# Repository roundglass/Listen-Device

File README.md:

# Roundglass Sustain Listen : Realtime Acoustic

## Monitoring

- **_Listen_** ​ is a modular acoustic station (device) and software / program to analyze sounds
- **_Listen_** ​is an end-end solution to collect sounds on the ground to infer intelligence
- **_Listen_** differs from other acoustic stations available in the market in its ease-of-use,
    set-up and portability
- It relies on solar-power, long-lasting battery and a plug-n-play communication system
    that would transmit data real-time to a console or App or Web interface.
- The data will be available real-time on smartphone/tablet through an application and
    would enable users to make informed decisions. Potential users are conservation and
    law enforcement personnel (forest department primarily) and NGOs and local
    communities who are interested in conserving their natural heritage.
- The app has capabilities to view data as graphs and in other forms of visualization. (Ex:
    used to observe trend of data over a requested time period like the sound
    characteristics.

## How does ​ Listen ​ work?

### Listen: working illustration

Listen isolates ‘sounds-of-interest’ from the surrounding or ambient sound. Sounds-of-interest
can be defined according to our needs - gunshots, dynamite blasts, motor vehicles, timber
felling, etc. The unit(Listen Mote) is installed in field and designed to blend in with the
surroundings - hidden in the tree canopy, etc. This can stay deployed for at least 4 weeks
without a battery change. There exists an option to connect it to a solar charger for longer
deployments. 

High-sensitivity microphones coupled with a data transmission system form the
field unit (Listen Mote). Information is received at a base station over cellular network.
The audio recording based on the programmed recording frequency is uploaded to our cloud
database which is linked to our cloud based virtual analytics system, once the system
determines that a particular recording is of interest (anomaly in the environment) then an alert is
sent out to the respective authority.

We foresee a need for these devices in the coming years owing to increased awareness
regarding conservation issues and also due to severe shortage of enforcement and patrol
personnel guarding our protected areas.

## Hardware 

### Roundglass Sustain Listen: components

**Microphones** ​: A high sensitivity microphone is used that will work for far field listening and has
digital gain to isolate noise amplification as in analog signal amplification.

**Form factor:** ​ Easy to conceal, hard shell polycarbonate, rounded edges, matte finish, no
external wiring or protruding antenna.

**Power source:** ​Solar powered with alternate power input for seasons and places with no
adequate solar radiation.

**Battery** ​: Li-ion pack can stay powered and deployed in field for at least 4 weeks without charge.

**Communication** ​: Wireless (GSM)

**Data** ​: App and Web based monitoring, configurable frequency and format of logging and
transmission.

**Switches** ​: Waterproof, dust-proof and insect-proof. No external switches.

**Mounting** ​: Compact system can be mounted on a mast or tripod of your choice.

## Technical Specifications

**Communication** ​: Global GSM

**Temperature** ​: -20 to 60 C

**Weatherproof** ​: IP 66/

**Battery:** ​ Rechargeable Li-ion battery.

**Solar Panel:** ​ Optional

**Alternate Power source** ​: Can plug a 6-12V external DC power supply (Optional)

**Application:** ​Android and iOS

## Applications

Protected areas are often vast, remote, with difficult terrain and severely understaffed to
effectively monitor and protect. With Roundglass Sustain Listen, we hope to plug in some of these gaps to
effectively monitor large areas and identify threats.

1. Detection of gunshots in protected areas - poaching and hunting increasingly rely on
    guns and is one of the leading causes of wildlife decline
2. Detection of dynamite fishing along rivers - illegal and highly destructive. The
    conservation and livelihood impacts of dynamite fishing is enormous
3. Detection of vehicular movement in protected areas - motor vehicles are used to illegally
    access areas for poaching, hunting and timber smuggling.
4. Another potential application (which we hope to address at a later date) is detection of
    wildfires

## Highlights​:

1. Detects, locates and alerts on threat sounds in less than 60 seconds.

2. Simple, affordable subscription service — no IT integration required

3. Get notified on your existing mobile phone via SMS / App notification.

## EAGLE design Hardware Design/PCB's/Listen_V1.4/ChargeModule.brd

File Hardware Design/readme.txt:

#Hardware Design

Schematics and PCB Design

Platform Eagle

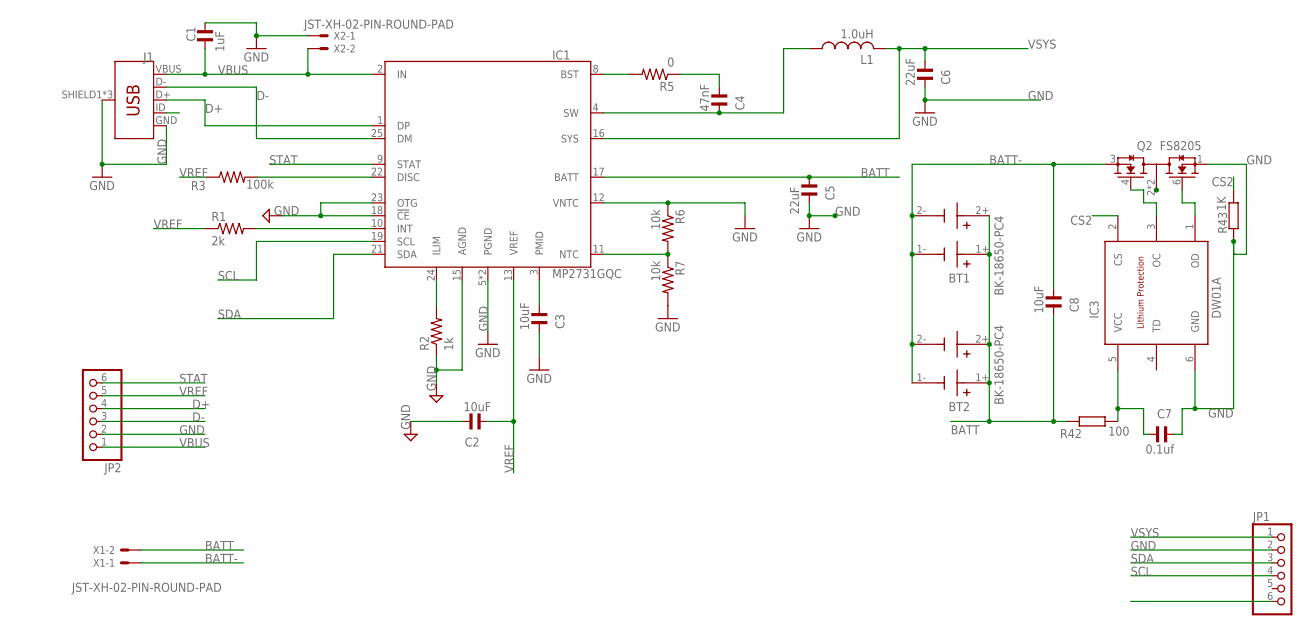
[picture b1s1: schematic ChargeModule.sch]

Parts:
BT1, BT2: BK-18650-PC4; BAT_BK-18650-PC4
C1: 1uF; RC-MASTER-SMD_C0805MP
C2, C3, C8: 10uF; RC-MASTER-SMD_C0805MP
C4: 47nF; RC-MASTER-SMD_C0805MP
C5, C6: 22uF; RC-MASTER-SMD_C0805MP
C7: 0.1uf; RC-MASTER-SMD_C0805MP
IC1: MP2731GQC; QFN-26-3.5
IC3: DW01A; SOT23-6
J1: USB_MICRO-B_FEMALE-SMT; USB-B-MICRO-SMD
JP1, JP2: PINHD-1X6JSTXH; JST-XH-06-PACKAGE-ROUND-PAD
L1: 1.0uH; POWER-CHOKE_WE-TPC
Q2: FS8205; SOT95P280X145-6N
R1: 2k; M0805
R2: 1k; M0805
R3: 100k; M0805
R5: 0; M0805
R6, R7: 10k; M0805
R42: 100; R0805
R43: 1K; R0805
X1, X2: JST-XH-02-PIN-ROUND-PAD; JST-XH-02-PACKAGE-ROUND-PAD

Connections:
BATT: BT1.1+, BT1.2+, BT2.1+, BT2.2+, C5.1, C8.2, IC1.17 (BATT), R42.2, X1.2
BATT-: BT1.1-, BT1.2-, BT2.1-, BT2.2-, C8.1, Q2.3 (S2), X1.1
CS2: IC3.2 (CS), R43.1
D+: IC1.1 (DP), J1.D+, JP2.4
D-: IC1.25 (DM), J1.D-, JP2.3
GND: C1.2, C2.2, C3.2, C5.2, C6.2, C7.2, IC1.5 (PGND), IC1.6 (PGND), IC1.12 (VNTC), IC1.15 (AGND), IC1.18 (!CE), IC1.23 (OTG), IC3.6 (GND), J1.GND, J1.SHIELD1 (SHIELD), J1.SHIELD2 (SHIELD), J1.SHIELD3 (SHIELD), JP1.2, JP2.2, Q2.1 (S1), R2.1, R6.1, R7.2, R43.2, X2.1
unnamed: IC1.24 (ILIM), R2.2
unnamed: IC1.10 (INT), R1.2
unnamed: IC1.22 (DISC), R3.2
unnamed: IC1.8 (BST), R5.2
unnamed: C3.1, IC1.3 (PMID)
unnamed: C4.1, R5.1
unnamed: C4.2, IC1.4 (SW), L1.1
unnamed: IC1.11 (NTC), R6.2, R7.1
unnamed: Q2.2 (D12), Q2.5 (D12)
unnamed: C7.1, IC3.5 (VCC), R42.1
unnamed: IC3.1 (OD), Q2.6 (G1)
unnamed: IC3.3 (OC), Q2.4 (G2)
SCL: IC1.19 (SCL), JP1.4
SDA: IC1.21 (SDA), JP1.3
STAT: IC1.9 (STAT), JP2.6
VBUS: C1.1, IC1.2 (IN), J1.VBUS, JP2.1, X2.2
VREF: C2.1, IC1.13 (VREF), JP2.5, R1.1, R3.1
VSYS: C6.1, IC1.16 (SYS), JP1.1, L1.2

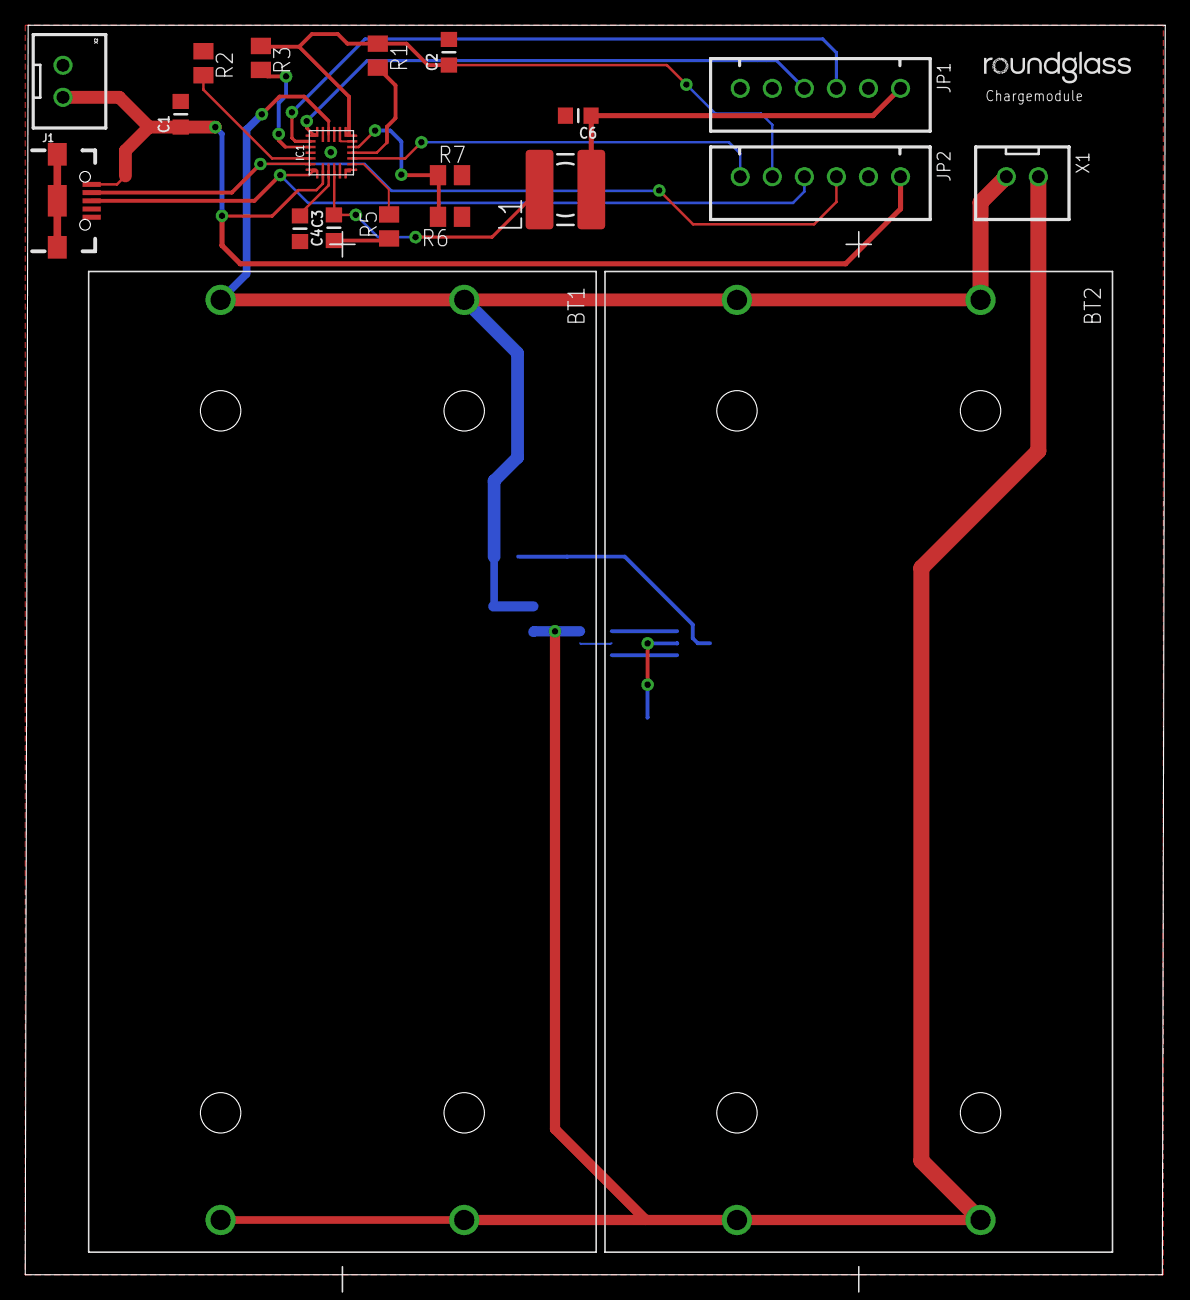
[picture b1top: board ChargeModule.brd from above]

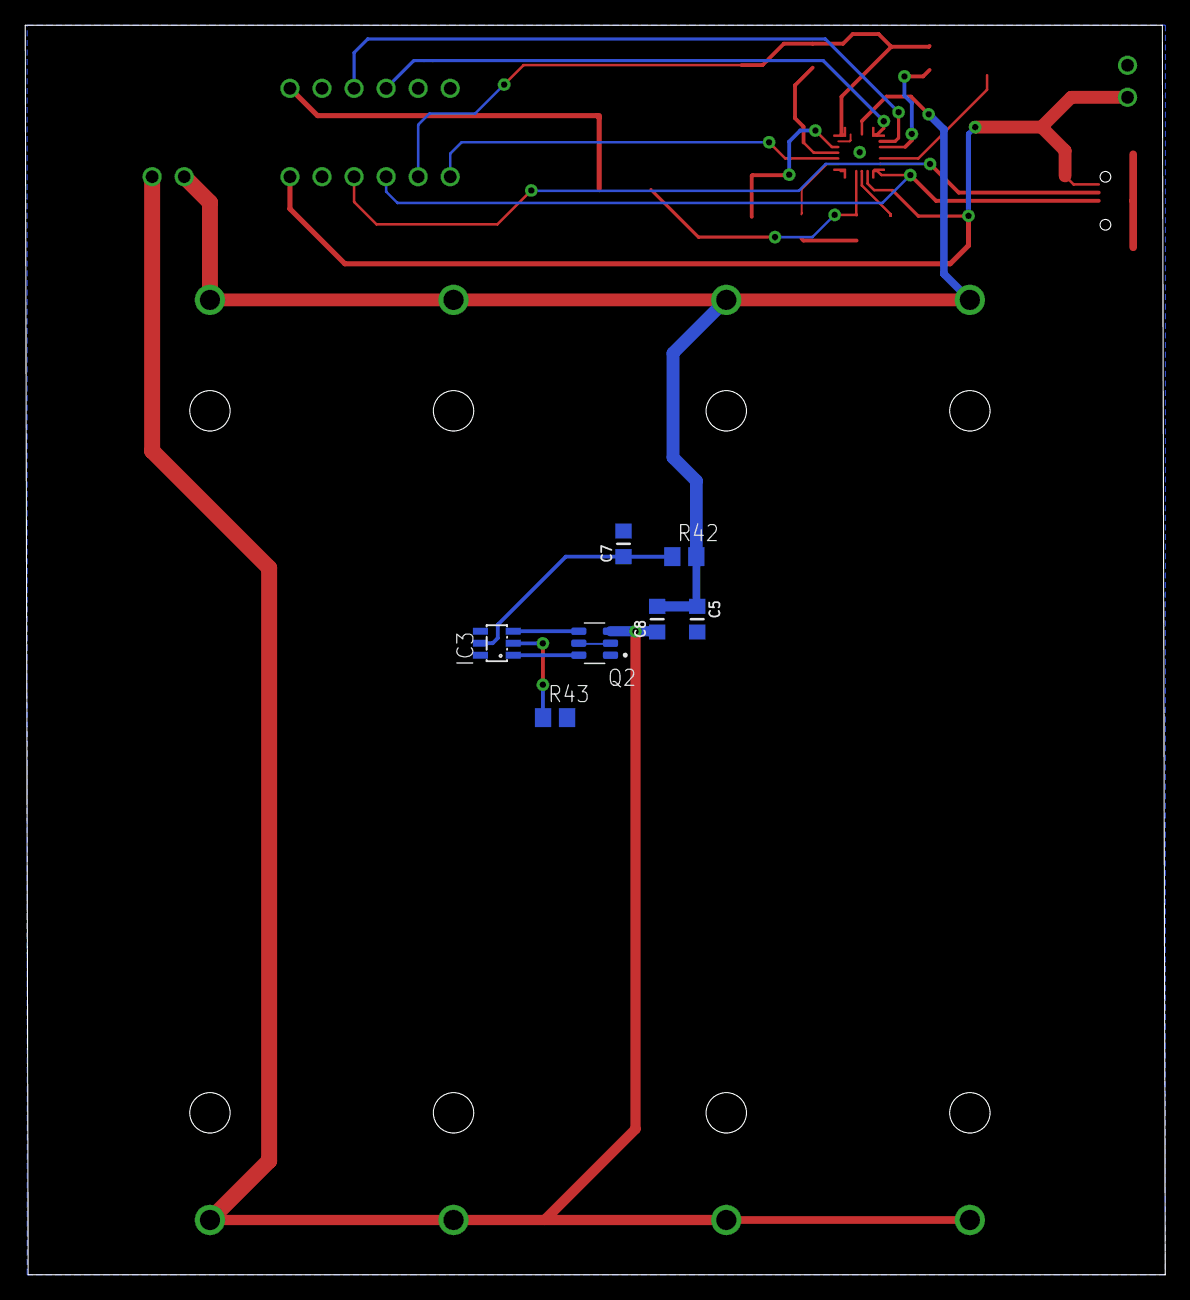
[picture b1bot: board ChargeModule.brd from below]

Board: 2 copper layers, 90.3 x 99.0 mm, 27 parts (7 on the bottom side), 24 nets.

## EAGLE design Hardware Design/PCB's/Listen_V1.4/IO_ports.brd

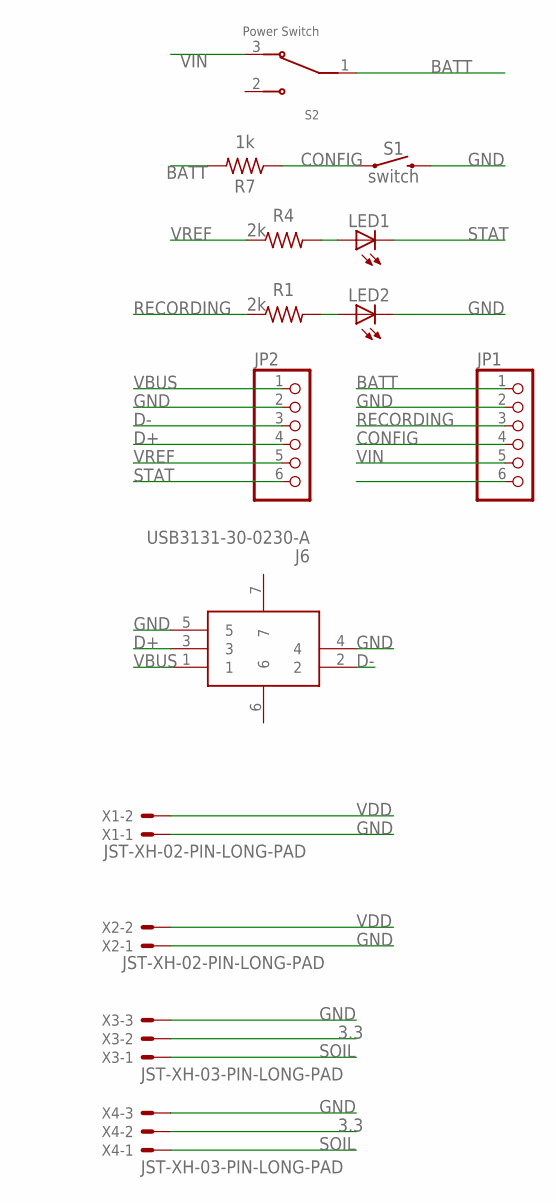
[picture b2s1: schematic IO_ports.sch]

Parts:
J6: USB3131-30-0230-A; USB3131300230A
JP1, JP2: PINHD-1X6JSTXH; JST-XH-06-PACKAGE-ROUND-PAD
LED1, LED2: LEDCHIP-LED0805; CHIP-LED0805
R1, R4: 2k; M0805
R7: 1k; RESC2012X65
S1: switch; TACTILE_SWITCH_PTH_6.0MM
S2: Power Switch; SW_MSS-102545-28A-D
X1, X2: JST-XH-02-PIN-LONG-PAD; JST-XH-02-PACKAGE-LONG-PAD
X3, X4: JST-XH-03-PIN-LONG-PAD; JST-XH-03-PACKAGE-LONG-PAD

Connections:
3.3: X3.2, X4.2
BATT: JP1.1, R7.2, S2.1
CONFIG: JP1.4, R7.1, S1.1
D+: J6.3, JP2.4
D-: J6.2, JP2.3
GND: J6.4, J6.5, JP1.2, JP2.2, LED2.C, S1.3 (2), X1.1, X2.1, X3.3, X4.3
unnamed: LED2.A, R1.2
unnamed: LED1.A, R4.2
RECORDING: JP1.3, R1.1
SOIL: X3.1, X4.1
STAT: JP2.6, LED1.C
VBUS: J6.1, JP2.1
VDD: X1.2, X2.2
VIN: JP1.5, S2.3
VREF: JP2.5, R4.1

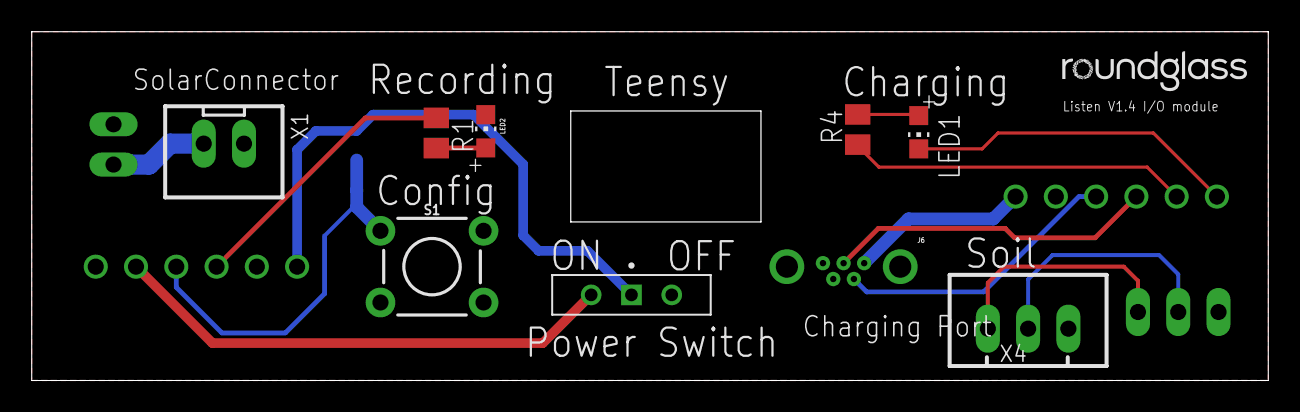
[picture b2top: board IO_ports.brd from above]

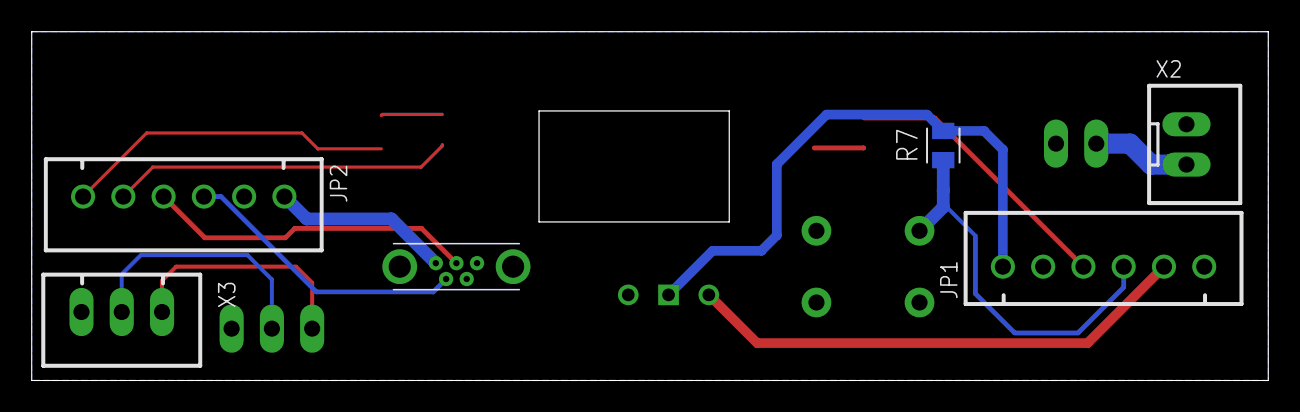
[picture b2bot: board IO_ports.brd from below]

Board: 2 copper layers, 78.0 x 22.0 mm, 14 parts (6 on the bottom side), 15 nets.

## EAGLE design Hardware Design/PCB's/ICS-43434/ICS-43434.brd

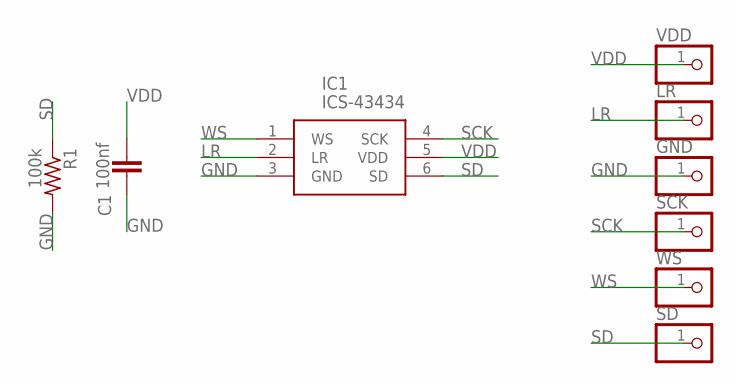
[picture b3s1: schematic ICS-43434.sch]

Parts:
C1: 100nf; CAP_0805
GND: PINHD-1X1CB; 1X01-CLEANBIG
IC1: ICS-43434; ICS43434
LR: PINHD-1X1CB; 1X01-CLEANBIG
R1: 100k; R0805
SCK: PINHD-1X1CB; 1X01-CLEANBIG
SD: PINHD-1X1CB; 1X01-CLEANBIG
VDD: PINHD-1X1CB; 1X01-CLEANBIG
WS: PINHD-1X1CB; 1X01-CLEANBIG

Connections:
GND: C1.1, GND.1, IC1.3 (GND), R1.2
LR: IC1.2 (LR), LR.1
SCK: IC1.4 (SCK), SCK.1
SD: IC1.6 (SD), R1.1, SD.1
VDD: C1.2, IC1.5 (VDD), VDD.1
WS: IC1.1 (WS), WS.1

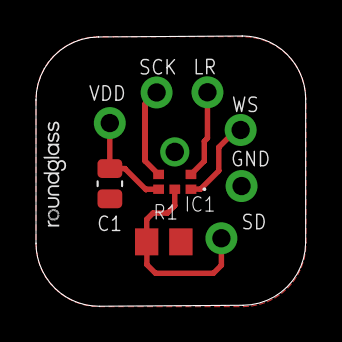
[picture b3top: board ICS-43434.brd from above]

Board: 2 copper layers, 15.0 x 15.0 mm, 9 parts (0 on the bottom side), 6 nets.

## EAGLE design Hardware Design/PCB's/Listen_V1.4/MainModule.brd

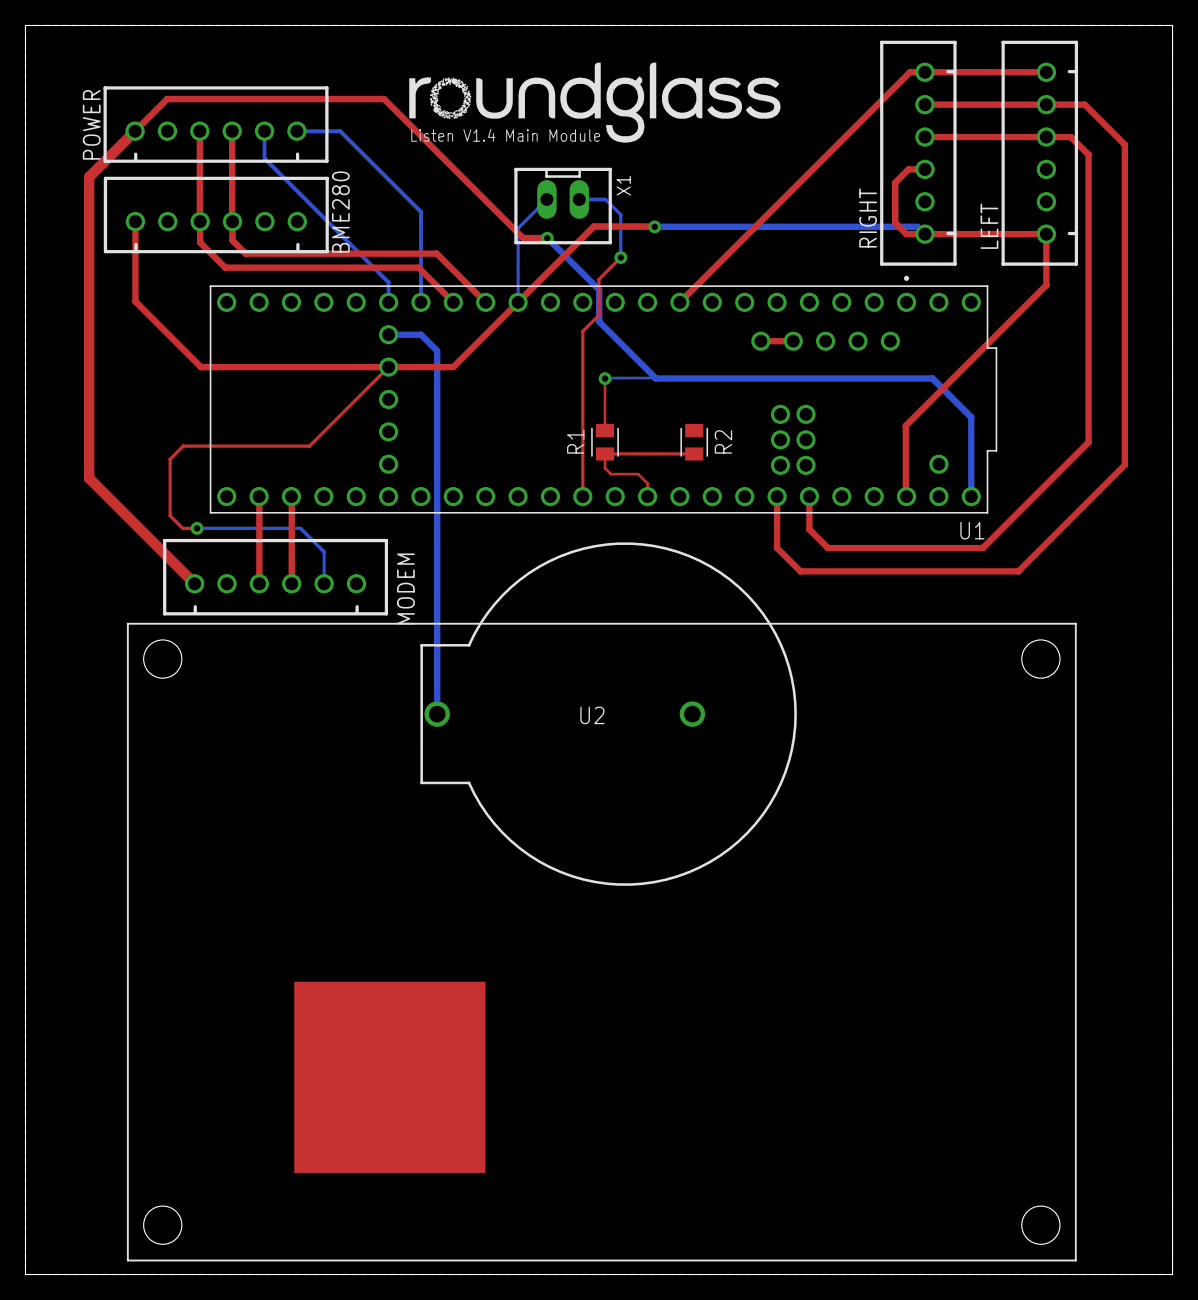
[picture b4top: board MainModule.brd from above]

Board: 2 copper layers, 90.0 x 98.0 mm, 12 parts (0 on the bottom side), 16 nets.

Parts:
BME280: JST-XH-06-PACKAGE-ROUND-PAD
LEFT: JST-XH-06-PACKAGE-ROUND-PAD
MODEM: JST-XH-06-PACKAGE-ROUND-PAD
POWER: JST-XH-06-PACKAGE-ROUND-PAD
R1, R2: 22k; RESC2012X65
RIGHT: JST-XH-06-PACKAGE-ROUND-PAD
U1: DEV-16771; MODULE_DEV-16771
U2: 1053
U$1: 4GMODULE4GMODULE; 4GMODULE
U$2: GPSANTENA
X1: SOIL; JST-XH-02-PACKAGE-LONG-PAD

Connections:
3.3V: BME280.1, LEFT.1, MODEM.5, RIGHT.1, RIGHT.3, U1.3.3V_1, U1.3.3V_2, U1.3.3V_3, X1.2
CONFIG: POWER.5, U1.27
GND: BME280.2, LEFT.2, LEFT.3, MODEM.2, MODEM.6, POWER.2, R2.1, RIGHT.2, U1.GND1, U1.GND2, U1.GND3, U1.GND4, U1.GND5, U2.1
unnamed: R1.1, R2.2, U1.16
RECORDING: POWER.6, U1.26
RX: MODEM.3, U1.34
SCK: LEFT.4, RIGHT.4, U1.21
SCL: BME280.4, POWER.4, U1.24
SD: LEFT.6, RIGHT.6, U1.8
SDA: BME280.3, POWER.3, U1.25
SOIL: U1.14, X1.1
TX: MODEM.4, U1.35
USB_GND: U1.USB_GND1, U1.USB_GND2
VBAT: U1.VBAT, U2.2
VIN: MODEM.1, POWER.1, R1.2, U1.VIN
WS: LEFT.5, RIGHT.5, U1.20

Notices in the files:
parts and their libraries:
SparkFun-Connectors: Licensing: Creative Commons ShareAlike 4.0 International - https://creativecommons.org/licenses/by-sa/4.0
